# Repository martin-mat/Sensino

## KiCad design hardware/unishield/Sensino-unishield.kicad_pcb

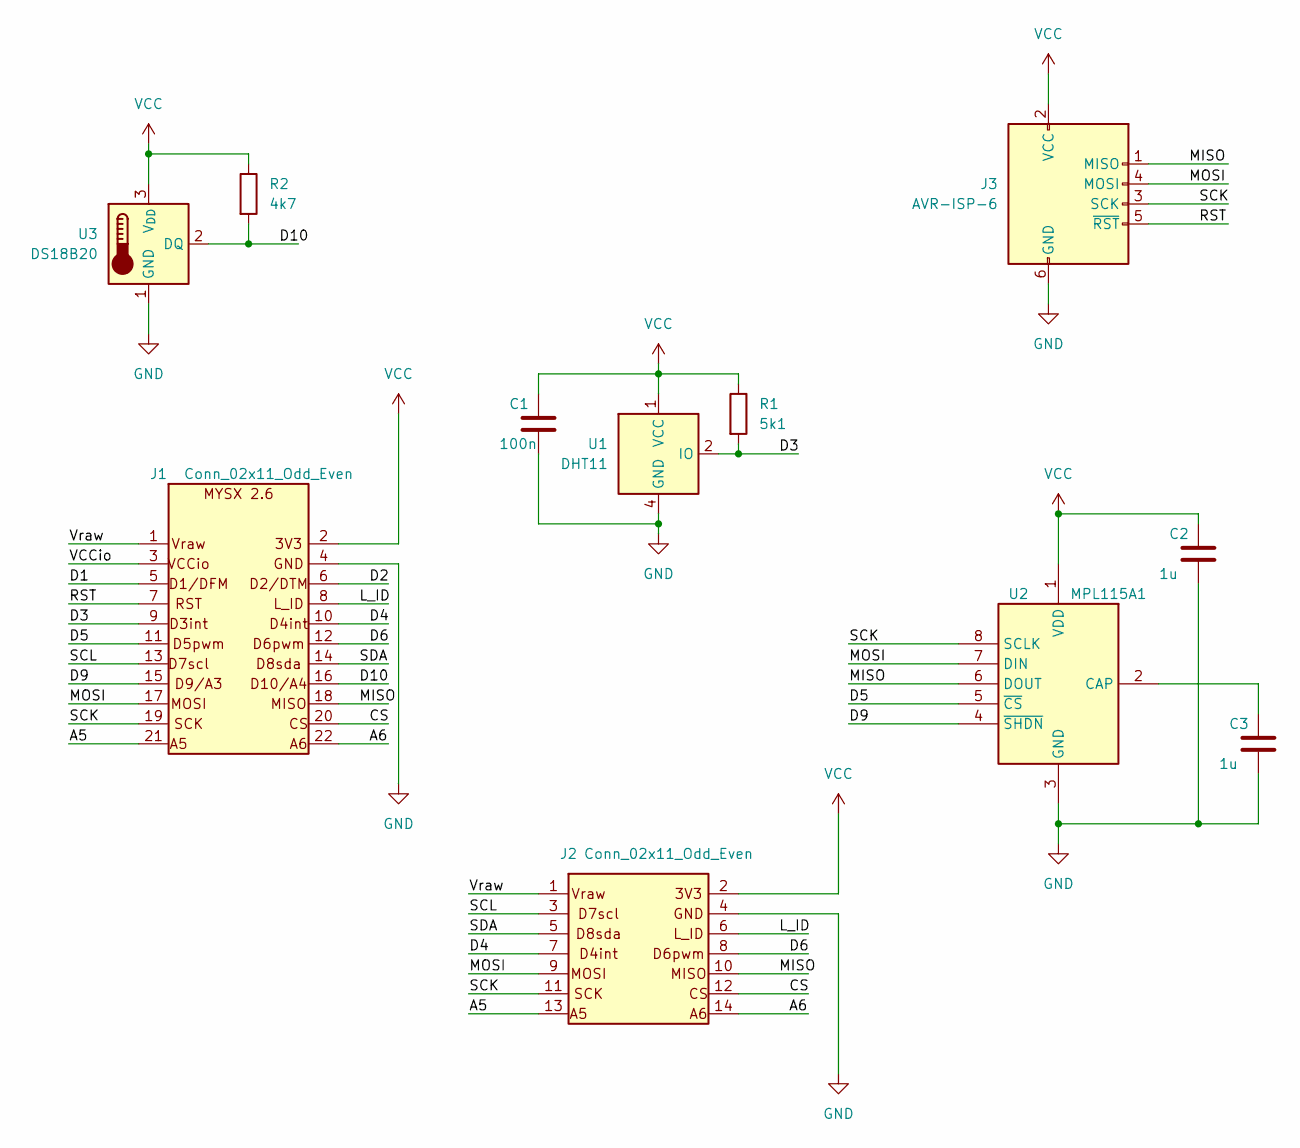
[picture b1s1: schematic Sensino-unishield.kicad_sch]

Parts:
C1: 100n; C_0805_2012Metric
C2, C3: 1u; C_0805_2012Metric
J1: Conn_02x11_Odd_Even; PinSocket_2x11_P2.54mm_Vertical
J2: Conn_02x11_Odd_Even; PinSocket_2x07_P2.54mm_Vertical
J3: AVR-ISP-6; PinSocket_2x03_P2.54mm_Vertical
R1: 5k1; R_0805_2012Metric
R2: 4k7; R_0805_2012Metric
U1: DHT11; Aosong_DHT11_5.5x12.0_P2.54mm
U2: MPL115A1; NXP_LGA-8_3x5mm_P1.25mm_H1.2mm
U3: DS18B20; TO-92_Inline

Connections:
/A5: J1.21, J2.13
/A6: J1.22, J2.14
/CS: J1.20, J2.12
/D1: J1.5
/D2: J1.6
/D3: J1.9, R1.2, U1.2 (IO)
/D4: J1.10, J2.7
/D5: J1.11, U2.5 (~CS)
/D6: J1.12, J2.8
/D9: J1.15, U2.4 (~SHDN)
/D10: J1.16, R2.2, U3.2 (DQ)
/L_ID: J1.8, J2.6
/MISO: J1.18, J2.10, J3.1 (MISO), U2.6 (DOUT)
/MOSI: J1.17, J2.9, J3.4 (MOSI), U2.7 (DIN)
/RST: J1.7, J3.5 (~RST)
/SCK: J1.19, J2.11, J3.3 (SCK), U2.8 (SCLK)
/SCL: J1.13, J2.3
/SDA: J1.14, J2.5
/VCCio: J1.3
/Vraw: J1.1, J2.1
GND: C1.2, C2.2, C3.2, J1.4, J2.4, J3.6 (GND), U1.4 (GND), U2.3 (GND), U3.1 (GND)
unnamed: C3.1, U2.2 (CAP)
VCC: C1.1, C2.1, J1.2, J2.2, J3.2 (VCC), R1.1, R2.1, U1.1 (VCC), U2.1 (VDD), U3.3 (V_{DD})

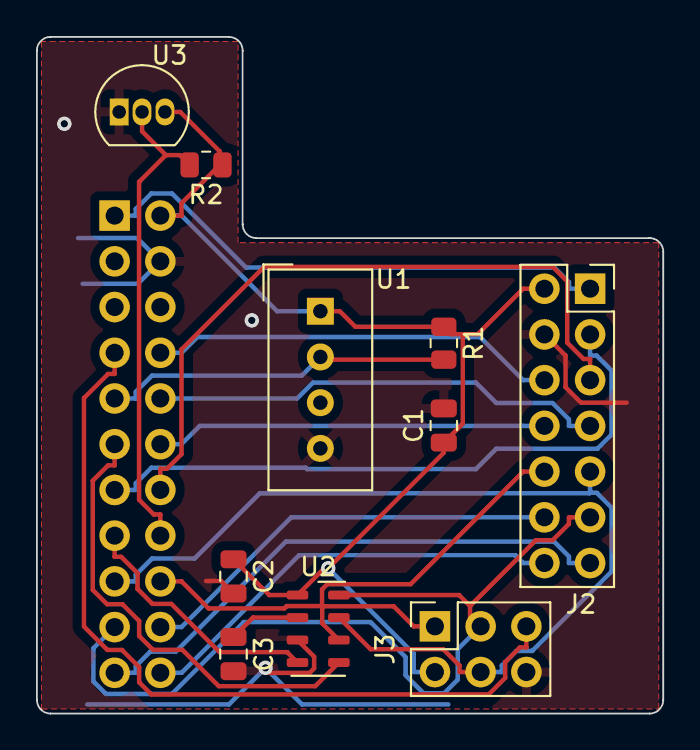
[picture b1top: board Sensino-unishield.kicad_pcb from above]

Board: 2 copper layers, 34.8 x 37.6 mm, 11 parts (1 on the bottom side), 20 nets.

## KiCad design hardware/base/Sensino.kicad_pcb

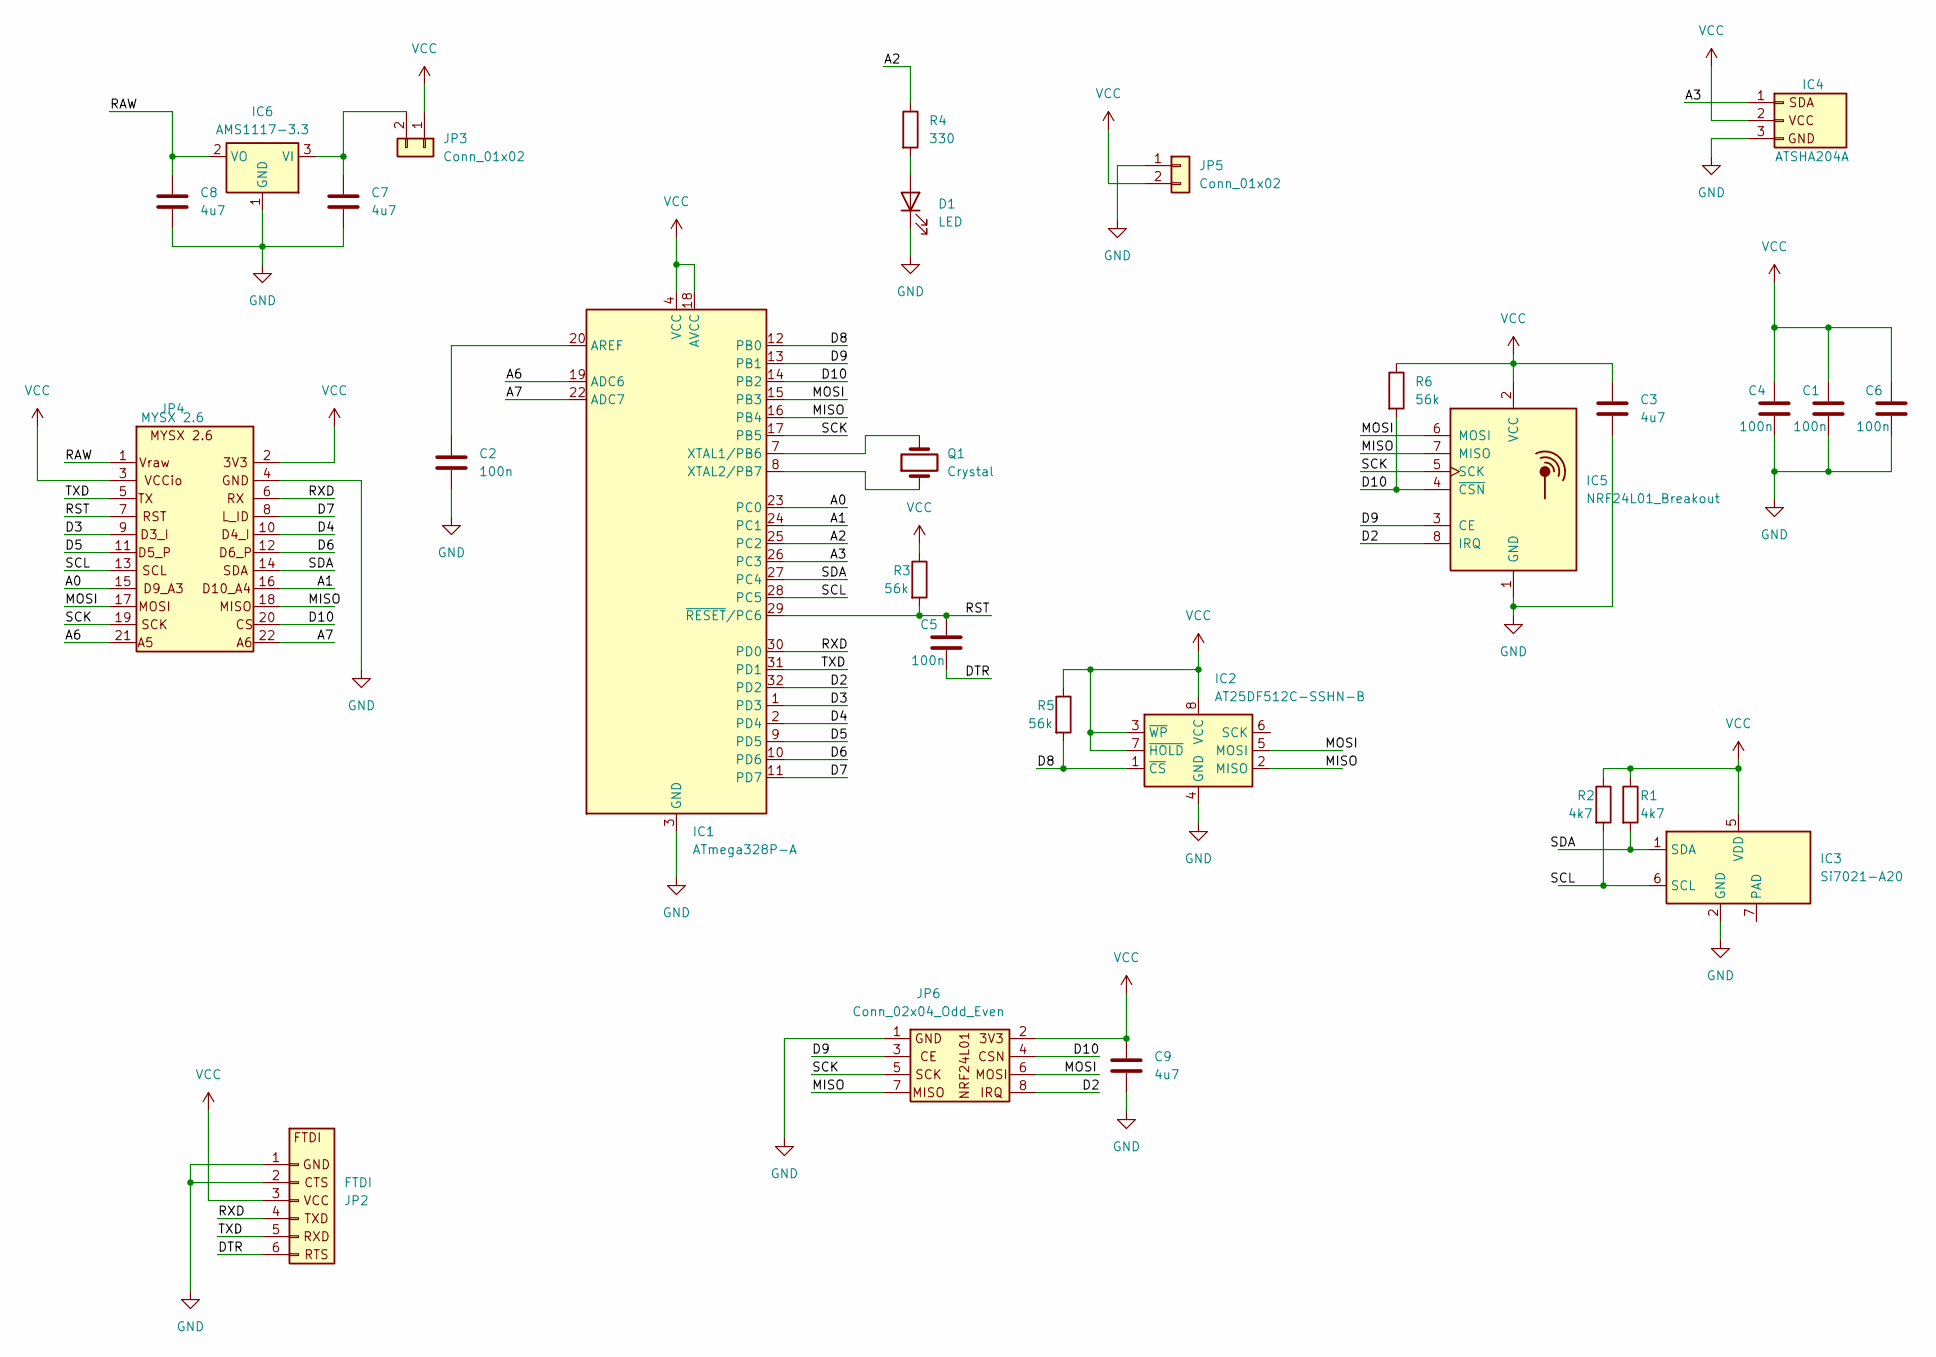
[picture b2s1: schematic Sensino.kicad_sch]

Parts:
C1, C2, C4, C5, C6: 100n; C_0805_2012Metric
C3, C7, C8, C9: 4u7; C_0805_2012Metric
D1: LED; R_0805_2012Metric
IC1: ATmega328P-A; TQFP-32_7x7mm_P0.8mm
IC2: AT25DF512C-SSHN-B; SO-8_3.9x4.9mm_P1.27mm
IC3: Si7021-A20; DFN-6-1EP_3x3mm_P1mm_EP1.5x2.4mm
IC4: ATSHA204A; SOT-23
IC5: NRF24L01_Breakout; NRF24L01-SMD
IC6: AMS1117-3.3; SOT-223-3_TabPin2
JP2: FTDI; PinHeader_1x06_P2.54mm_Horizontal
JP3: Conn_01x02; SolderJumper-2_P1.3mm_Open_RoundedPad1.0x1.5mm
JP4: MYSX 2.6; PinHeader_2x11_P2.54mm_Vertical
JP5: Conn_01x02; PinHeader_1x02_P2.54mm_Vertical
JP6: Conn_02x04_Odd_Even; PinHeader_2x04_P2.54mm_Vertical
Q1: Crystal; Crystal_SMD_3215-2Pin_3.2x1.5mm
R1, R2: 4k7; R_0805_2012Metric
R3, R5, R6: 56k; R_0805_2012Metric
R4: 330; R_0805_2012Metric

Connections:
/A0: IC1.23 (PC0), JP4.15
/A1: IC1.24 (PC1), JP4.16
/A2: IC1.25 (PC2), R4.1
/A3: IC1.26 (PC3), IC4.1 (SDA)
/A6: IC1.19 (ADC6), JP4.21
/A7: IC1.22 (ADC7), JP4.22
/D2: IC1.32 (PD2), IC5.8 (IRQ), JP6.8
/D3: IC1.1 (PD3), JP4.9
/D4: IC1.2 (PD4), JP4.10
/D5: IC1.9 (PD5), JP4.11
/D6: IC1.10 (PD6), JP4.12
/D7: IC1.11 (PD7), JP4.8
/D8: IC1.12 (PB0), IC2.1 (~CS), R5.2
/D9: IC1.13 (PB1), IC5.3 (CE), JP6.3
/D10: IC1.14 (PB2), IC5.4 (~CSN), JP4.20, JP6.4, R6.2
/DTR: C5.2, JP2.6
/MISO: IC1.16 (PB4), IC2.2 (MISO), IC5.7 (MISO), JP4.18, JP6.7
/MOSI: IC1.15 (PB3), IC2.5 (MOSI), IC5.6 (MOSI), JP4.17, JP6.6
/RAW: C8.1, IC6.2 (VO), JP4.1
/RST: C5.1, IC1.29 (~RESET/PC6), JP4.7, R3.2
/RXD: IC1.30 (PD0), JP2.4, JP4.6
/SCK: IC1.17 (PB5), IC5.5 (SCK), JP4.19, JP6.5
/SCL: IC1.28 (PC5), JP4.13
/SDA: IC1.27 (PC4), JP4.14
/TXD: IC1.31 (PD1), JP2.5, JP4.5
GND: C1.2, C2.2, C3.2, C4.2, C6.2, C7.2, C8.2, C9.2, D1.1 (K), IC1.3 (GND), IC1.5 (GND), IC1.21 (GND), IC2.4 (GND), IC3.2 (GND), IC4.3 (GND), IC5.1 (GND), IC6.1 (GND), JP2.1 (GND), JP2.2, JP4.4, JP5.1, JP6.1
unnamed: D1.2 (A), R4.2
unnamed: C2.1, IC1.20 (AREF)
unnamed: IC1.7 (XTAL1/PB6), Q1.2
unnamed: IC1.8 (XTAL2/PB7), Q1.1
unnamed: IC3.6 (SCL), R2.2
unnamed: IC3.1 (SDA), R1.2
unnamed: C7.1, IC6.3 (VI), JP3.2
VCC: C1.1, C3.1, C4.1, C6.1, C9.1, IC1.4 (VCC), IC1.6 (VCC), IC1.18 (AVCC), IC2.3 (~WP), IC2.7 (~HOLD), IC2.8 (VCC), IC3.5 (VDD), IC4.2 (VCC), IC5.2 (VCC), JP2.3, JP3.1, JP4.2, JP4.3, JP5.2, JP6.2, R1.1, R2.1, R3.1, R5.1, R6.1

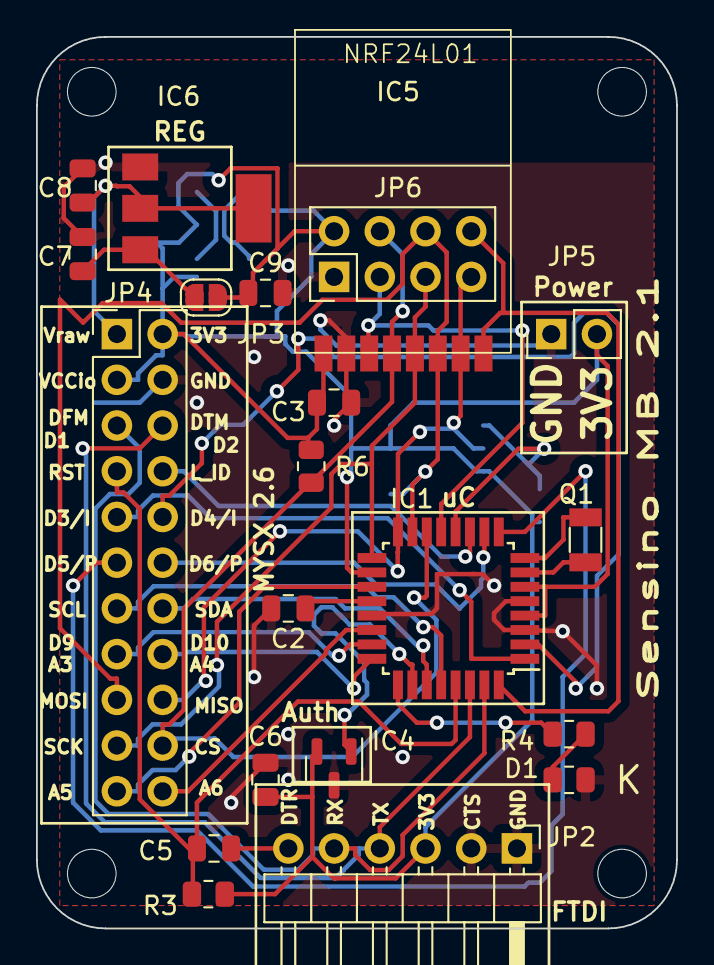
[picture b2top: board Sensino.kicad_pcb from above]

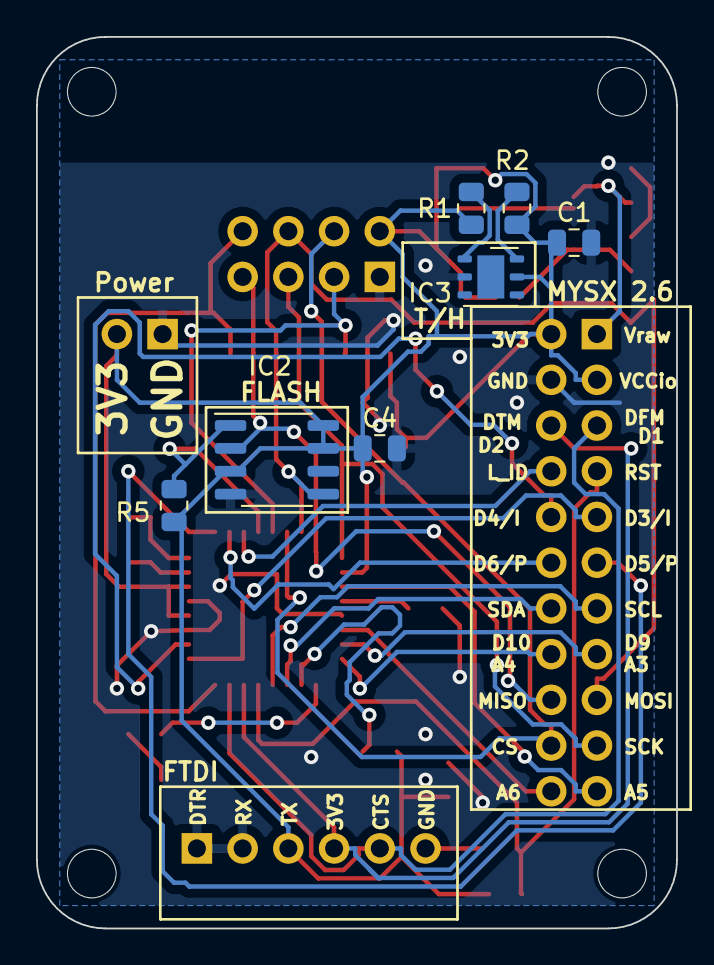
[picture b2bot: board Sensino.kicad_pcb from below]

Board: 2 copper layers, 35.6 x 49.5 mm, 28 parts (7 on the bottom side), 34 nets.

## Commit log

2015-03-18 version 1.0
2023-12-06 Complete rework
    Migrate to KiCad. Rework design to be compatible
    with Sensebender Micro. Change shield connector
    to MYSX 2.6.
